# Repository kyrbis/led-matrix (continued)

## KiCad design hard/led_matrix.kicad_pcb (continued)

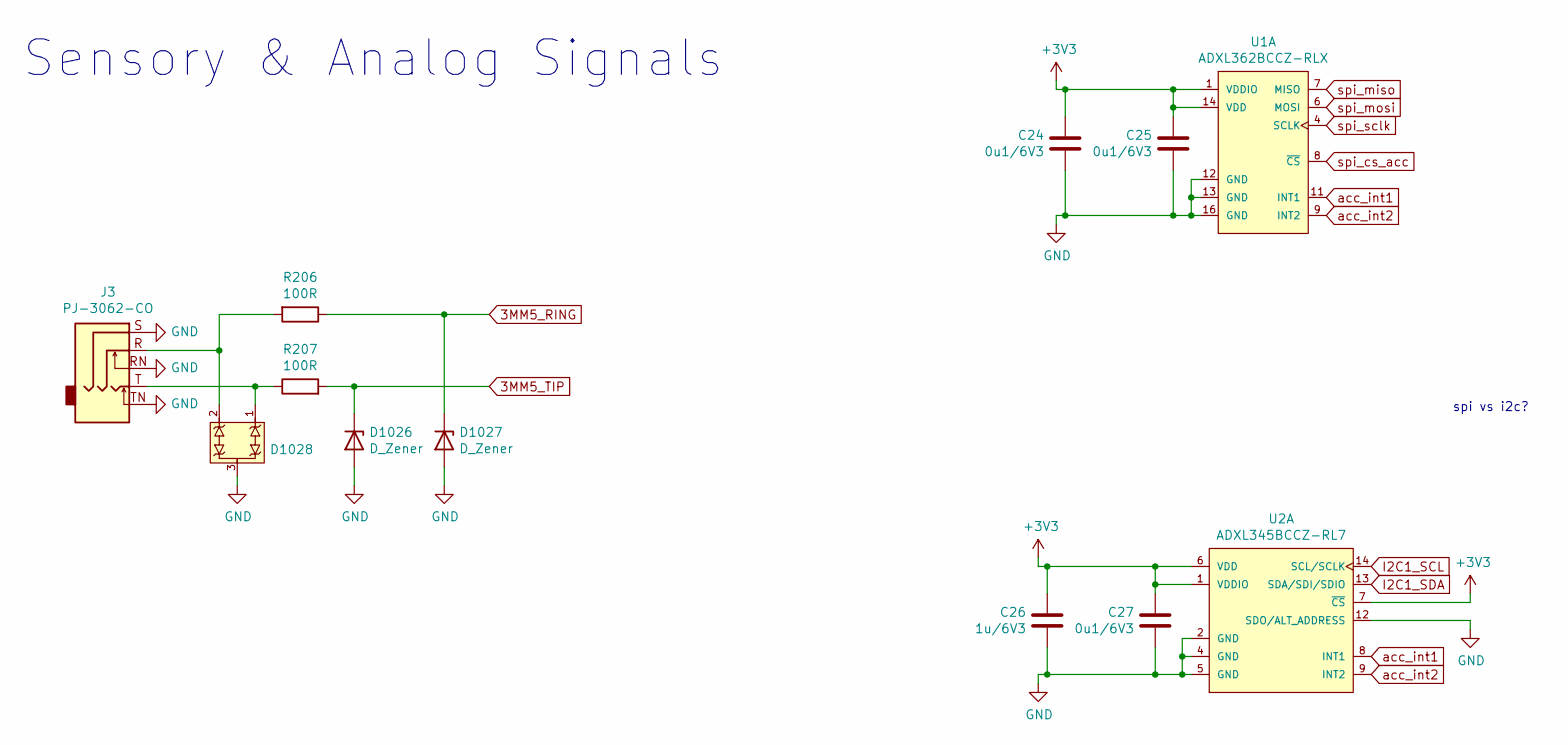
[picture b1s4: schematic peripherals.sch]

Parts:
C24, C25, C27: 0u1/6V3; C_0402_1005Metric
C26: 1u/6V3; C_0603_1608Metric
D1026, D1027: D_Zener; D_MiniMELF; MPN Semtech; JLCPCB_Part_Number C8056
D1028: PSM712-LF-T7; SOT-23; MPN PSM712-LF-T7; JLCPCB_Part_Number C32677
J3: PJ-3062-CO; Connectors_XKB Connectivity_PJ-3062-CO; MPN PJ-3062-CO; JLCPCB_Part_Number C319113
R206, R207: 100R; R_0603_1608Metric
U1: ADXL362BCCZ-RLX; Sensors_AnalogDevices_ADXL362BCCZ-RX; MPN ADXL362BCCZ-RL; DigiKey_Part_Number ADXL362BCCZ-RL7CT-ND
U2: ADXL345BCCZ-RL7; Sensors_AnalogDevices_ADXL345BCCZ-RL; MPN ADXL345BCCZ-RL7; DigiKey_Part_Number ADXL345BCCZ-RLCT-ND

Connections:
+3V3: C24.2, C25.2, C26.2, C27.2, U1.1 (VDDIO), U1.14 (VDD), U2.1 (VDDIO), U2.6 (VDD), U2.7 (~CS~); also elsewhere on the board
GND: C24.1, C25.1, C26.1, C27.1, D1026.2 (A), D1027.2 (A), D1028.3, J3.RN, J3.S, J3.TN, U1.12 (GND), U1.13 (GND), U1.16 (GND), U2.2 (GND), U2.4 (GND), U2.5 (GND), U2.12 (SDO/ALT_ADDRESS); also elsewhere on the board
I2C1_SCL: U2.14 (SCL/SCLK); also elsewhere on the board
I2C1_SDA: U2.13 (SDA/SDI/SDIO); also elsewhere on the board
unnamed: D1028.1, J3.T, R207.1
unnamed: D1028.2, J3.R, R206.2
acc_int1: U1.11 (INT1), U2.8 (INT1)
acc_int2: U1.9 (INT2), U2.9 (INT2)
analog_ring: D1027.1 (K), R206.1
analog_tip: D1026.1 (K), R207.2

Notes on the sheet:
spi vs i2c?
Sensory & Analog Signals

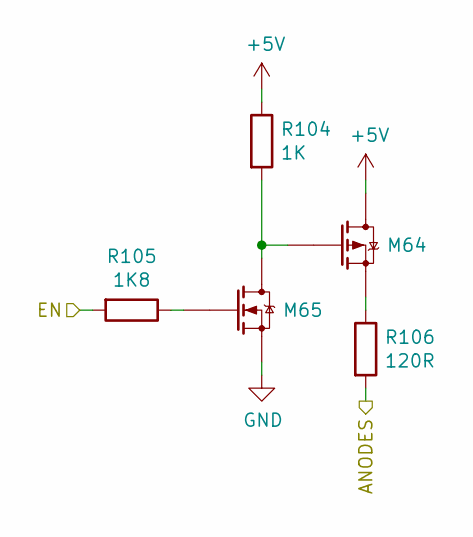
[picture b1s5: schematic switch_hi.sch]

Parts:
M2: IRLML6402TRPBF; SOT-23; Mouser_Part_Number 942-IRLML6402TRPBF; DigiKey_Part_Number IRLML6402PBFTR-ND
M3: 2N7002,215; SOT-23; MPN 2N7002,215; JLCPCB_Part_Number C65189
R11: 1K; R_0402_1005Metric
R12: 1K8; R_0402_1005Metric
R13: 120R; R_1210_3225Metric

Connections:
+5V: M2.3 (D), R11.1; also elsewhere on the board
/led matrix/common anode/ANODES: R13.2; also elsewhere on the board
GND: M3.2 (S); also elsewhere on the board
unnamed: M2.1 (G), M3.3 (D), R11.2
unnamed: M2.2 (S), R13.1
unnamed: M3.1 (G), R12.1
x0: R12.2; also elsewhere on the board

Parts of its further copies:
M4, M6, M8, M10, M12, M14, M16, M18, M20, M22, M24, M26, M28, M30, M32, M34, M36, M38, M40, M42, M44, M46, M48, M50, M52, M54, M56, M58, M60, M62, M64: IRLML6402TRPBF; SOT-23; Mouser_Part_Number 942-IRLML6402TRPBF; DigiKey_Part_Number IRLML6402PBFTR-ND
M5, M7, M9, M11, M13, M15, M17, M19, M21, M23, M25, M27, M29, M31, M33, M35, M37, M39, M41, M43, M45, M47, M49, M51, M53, M55, M57, M59, M61, M63, M65: 2N7002,215; SOT-23; MPN 2N7002,215; JLCPCB_Part_Number C65189
R14, R17, R20, R23, R26, R29, R32, R35, R38, R41, R44, R47, R50, R53, R56, R59, R62, R65, R68, R71, R74, R77, R80, R83, R86, R89, R92, R95, R98, R101, R104: 1K; R_0402_1005Metric
R15, R18, R21, R24, R27, R30, R33, R36, R39, R42, R45, R48, R51, R54, R57, R60, R63, R66, R69, R72, R75, R78, R81, R84, R87, R90, R93, R96, R99, R102, R105: 1K8; R_0402_1005Metric
R16, R19, R22, R25, R28, R31, R34, R37, R40, R43, R46, R49, R52, R55, R58, R61, R64, R67, R70, R73, R76, R79, R82, R85, R88, R91, R94, R97, R100, R103, R106: 120R; R_1210_3225Metric

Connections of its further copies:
+5V: M4.3 (D), M6.3 (D), M8.3 (D), M10.3 (D), M12.3 (D), M14.3 (D), M16.3 (D), M18.3 (D), M20.3 (D), M22.3 (D), M24.3 (D), M26.3 (D), M28.3 (D), M30.3 (D), M32.3 (D), M34.3 (D), M36.3 (D), M38.3 (D), M40.3 (D), M42.3 (D), M44.3 (D), M46.3 (D), M48.3 (D), M50.3 (D), M52.3 (D), M54.3 (D), M56.3 (D), M58.3 (D), M60.3 (D), M62.3 (D), M64.3 (D), R14.1, R17.1, R20.1, R23.1, R26.1, R29.1, R32.1, R35.1, R38.1, R41.1, R44.1, R47.1, R50.1, R53.1, R56.1, R59.1, R62.1, R65.1, R68.1, R71.1, R74.1, R77.1, R80.1, R83.1, R86.1, R89.1, R92.1, R95.1, R98.1, R101.1, R104.1; also elsewhere on the board
/led matrix/sheet9E2197FD/ANODES: R16.2; also elsewhere on the board
/led matrix/sheetA3FD3BF7/ANODES: R31.2; also elsewhere on the board
/led matrix/sheetA3FD3BF8/ANODES: R34.2; also elsewhere on the board
/led matrix/sheetA4B98B8A/ANODES: R49.2; also elsewhere on the board
/led matrix/sheetA4B98B8B/ANODES: R52.2; also elsewhere on the board
/led matrix/sheetA4B98B8C/ANODES: R55.2; also elsewhere on the board
/led matrix/sheetA4B98B8D/ANODES: R58.2; also elsewhere on the board
/led matrix/sheetA4B98B86/ANODES: R37.2; also elsewhere on the board
/led matrix/sheetA4B98B87/ANODES: R40.2; also elsewhere on the board
/led matrix/sheetA4B98B88/ANODES: R43.2; also elsewhere on the board
/led matrix/sheetA4B98B89/ANODES: R46.2; also elsewhere on the board
/led matrix/sheetA10E8493/ANODES: R19.2; also elsewhere on the board
/led matrix/sheetA10E8494/ANODES: R22.2; also elsewhere on the board
/led matrix/sheetA341C37F/ANODES: R25.2; also elsewhere on the board
/led matrix/sheetA341C380/ANODES: R28.2; also elsewhere on the board
/led matrix/sheetA575BE8D/ANODES: R61.2; also elsewhere on the board
/led matrix/sheetA575BE8E/ANODES: R64.2; also elsewhere on the board
/led matrix/sheetA575BE8F/ANODES: R67.2; also elsewhere on the board
/led matrix/sheetA575BE9A/ANODES: R100.2; also elsewhere on the board
/led matrix/sheetA575BE9B/ANODES: R103.2; also elsewhere on the board
/led matrix/sheetA575BE9C/ANODES: R106.2; also elsewhere on the board
/led matrix/sheetA575BE90/ANODES: R70.2; also elsewhere on the board
/led matrix/sheetA575BE91/ANODES: R73.2; also elsewhere on the board
/led matrix/sheetA575BE92/ANODES: R76.2; also elsewhere on the board
/led matrix/sheetA575BE93/ANODES: R79.2; also elsewhere on the board
/led matrix/sheetA575BE94/ANODES: R82.2; also elsewhere on the board
/led matrix/sheetA575BE95/ANODES: R85.2; also elsewhere on the board
/led matrix/sheetA575BE96/ANODES: R88.2; also elsewhere on the board
/led matrix/sheetA575BE97/ANODES: R91.2; also elsewhere on the board
/led matrix/sheetA575BE98/ANODES: R94.2; also elsewhere on the board
/led matrix/sheetA575BE99/ANODES: R97.2; also elsewhere on the board
GND: M5.2 (S), M7.2 (S), M9.2 (S), M11.2 (S), M13.2 (S), M15.2 (S), M17.2 (S), M19.2 (S), M21.2 (S), M23.2 (S), M25.2 (S), M27.2 (S), M29.2 (S), M31.2 (S), M33.2 (S), M35.2 (S), M37.2 (S), M39.2 (S), M41.2 (S), M43.2 (S), M45.2 (S), M47.2 (S), M49.2 (S), M51.2 (S), M53.2 (S), M55.2 (S), M57.2 (S), M59.2 (S), M61.2 (S), M63.2 (S), M65.2 (S); also elsewhere on the board
unnamed: M4.1 (G), M5.3 (D), R14.2
unnamed: M4.2 (S), R16.1
unnamed: M5.1 (G), R15.1
unnamed: M6.1 (G), M7.3 (D), R17.2
unnamed: M6.2 (S), R19.1
unnamed: M7.1 (G), R18.1
unnamed: M8.1 (G), M9.3 (D), R20.2
unnamed: M8.2 (S), R22.1
unnamed: M9.1 (G), R21.1
unnamed: M10.1 (G), M11.3 (D), R23.2
unnamed: M10.2 (S), R25.1
unnamed: M11.1 (G), R24.1
unnamed: M12.1 (G), M13.3 (D), R26.2
unnamed: M12.2 (S), R28.1
unnamed: M13.1 (G), R27.1
unnamed: M14.1 (G), M15.3 (D), R29.2
unnamed: M14.2 (S), R31.1
unnamed: M15.1 (G), R30.1
unnamed: M16.1 (G), M17.3 (D), R32.2
unnamed: M16.2 (S), R34.1
unnamed: M17.1 (G), R33.1
unnamed: M18.1 (G), M19.3 (D), R35.2
unnamed: M18.2 (S), R37.1
unnamed: M19.1 (G), R36.1
unnamed: M20.1 (G), M21.3 (D), R38.2
unnamed: M20.2 (S), R40.1
unnamed: M21.1 (G), R39.1
unnamed: M22.1 (G), M23.3 (D), R41.2
unnamed: M22.2 (S), R43.1
unnamed: M23.1 (G), R42.1
unnamed: M24.1 (G), M25.3 (D), R44.2
unnamed: M24.2 (S), R46.1
unnamed: M25.1 (G), R45.1
unnamed: M26.1 (G), M27.3 (D), R47.2
unnamed: M26.2 (S), R49.1
unnamed: M27.1 (G), R48.1
unnamed: M28.1 (G), M29.3 (D), R50.2
unnamed: M28.2 (S), R52.1
unnamed: M29.1 (G), R51.1
unnamed: M30.1 (G), M31.3 (D), R53.2
unnamed: M30.2 (S), R55.1
unnamed: M31.1 (G), R54.1
unnamed: M32.1 (G), M33.3 (D), R56.2
unnamed: M32.2 (S), R58.1
unnamed: M33.1 (G), R57.1
unnamed: M34.1 (G), M35.3 (D), R59.2
unnamed: M34.2 (S), R61.1
unnamed: M35.1 (G), R60.1
unnamed: M36.1 (G), M37.3 (D), R62.2
unnamed: M36.2 (S), R64.1
unnamed: M37.1 (G), R63.1
unnamed: M38.1 (G), M39.3 (D), R65.2
unnamed: M38.2 (S), R67.1
unnamed: M39.1 (G), R66.1
unnamed: M40.1 (G), M41.3 (D), R68.2
unnamed: M40.2 (S), R70.1
unnamed: M41.1 (G), R69.1
unnamed: M42.1 (G), M43.3 (D), R71.2
unnamed: M42.2 (S), R73.1
unnamed: M43.1 (G), R72.1
unnamed: M44.1 (G), M45.3 (D), R74.2
unnamed: M44.2 (S), R76.1
unnamed: M45.1 (G), R75.1
unnamed: M46.1 (G), M47.3 (D), R77.2
unnamed: M46.2 (S), R79.1
unnamed: M47.1 (G), R78.1
unnamed: M48.1 (G), M49.3 (D), R80.2
unnamed: M48.2 (S), R82.1
unnamed: M49.1 (G), R81.1
unnamed: M50.1 (G), M51.3 (D), R83.2
unnamed: M50.2 (S), R85.1
unnamed: M51.1 (G), R84.1
unnamed: M52.1 (G), M53.3 (D), R86.2
unnamed: M52.2 (S), R88.1
unnamed: M53.1 (G), R87.1
unnamed: M54.1 (G), M55.3 (D), R89.2
unnamed: M54.2 (S), R91.1
unnamed: M55.1 (G), R90.1
unnamed: M56.1 (G), M57.3 (D), R92.2
unnamed: M56.2 (S), R94.1
unnamed: M57.1 (G), R93.1
unnamed: M58.1 (G), M59.3 (D), R95.2
unnamed: M58.2 (S), R97.1
unnamed: M59.1 (G), R96.1
unnamed: M60.1 (G), M61.3 (D), R98.2
unnamed: M60.2 (S), R100.1
unnamed: M61.1 (G), R99.1
unnamed: M62.1 (G), M63.3 (D), R101.2
unnamed: M62.2 (S), R103.1
unnamed: M63.1 (G), R102.1
unnamed: M64.1 (G), M65.3 (D), R104.2
unnamed: M64.2 (S), R106.1
unnamed: M65.1 (G), R105.1
SWCLK: R54.2; also elsewhere on the board
SWDIO: R51.2; also elsewhere on the board
x1: R15.2; also elsewhere on the board
x2: R18.2; also elsewhere on the board
x3: R21.2; also elsewhere on the board
x4: R24.2; also elsewhere on the board
x5: R27.2; also elsewhere on the board
x6: R30.2; also elsewhere on the board
x7: R33.2; also elsewhere on the board
x8: R36.2; also elsewhere on the board
x9: R39.2; also elsewhere on the board
x10: R42.2; also elsewhere on the board
x11: R45.2; also elsewhere on the board
x12: R48.2; also elsewhere on the board
x15: R57.2; also elsewhere on the board
x16: R60.2; also elsewhere on the board
x17: R63.2; also elsewhere on the board
x18: R66.2; also elsewhere on the board
x19: R69.2; also elsewhere on the board
x20: R72.2; also elsewhere on the board
x21: R75.2; also elsewhere on the board
x22: R78.2; also elsewhere on the board
x23: R81.2; also elsewhere on the board
x24: R84.2; also elsewhere on the board
x25: R87.2; also elsewhere on the board
x26: R90.2; also elsewhere on the board
x27: R93.2; also elsewhere on the board
x28: R96.2; also elsewhere on the board
x29: R99.2; also elsewhere on the board
x30: R102.2; also elsewhere on the board
x31: R105.2; also elsewhere on the board

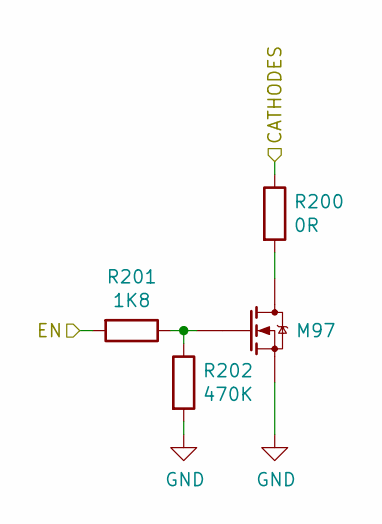
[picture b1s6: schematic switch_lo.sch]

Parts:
M66: IRLML0030TRPBF; SOT-23; Mouser_Part_Number 942-IRLML0030TRPBF; DigiKey_Part_Number IRLML0030TRPBFCT-ND
R107: 0R; R_1210_3225Metric
R108: 1K8; R_0402_1005Metric
R109: 470K; R_0402_1005Metric

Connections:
/led matrix/common cathode/CATHODES: R107.1; also elsewhere on the board
GND: M66.2 (S), R109.2; also elsewhere on the board
unnamed: M66.1 (G), R108.1, R109.1
unnamed: M66.3 (D), R107.2
y0: R108.2; also elsewhere on the board

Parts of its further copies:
M67, M68, M69, M70, M71, M72, M73, M74, M75, M76, M77, M78, M79, M80, M81, M82, M83, M84, M85, M86, M87, M88, M89, M90, M91, M92, M93, M94, M95, M96, M97: IRLML0030TRPBF; SOT-23; Mouser_Part_Number 942-IRLML0030TRPBF; DigiKey_Part_Number IRLML0030TRPBFCT-ND
R110, R113, R116, R119, R122, R125, R128, R131, R134, R137, R140, R143, R146, R149, R152, R155, R158, R161, R164, R167, R170, R173, R176, R179, R182, R185, R188, R191, R194, R197, R200: 0R; R_1210_3225Metric
R111, R114, R117, R120, R123, R126, R129, R132, R135, R138, R141, R144, R147, R150, R153, R156, R159, R162, R165, R168, R171, R174, R177, R180, R183, R186, R189, R192, R195, R198, R201: 1K8; R_0402_1005Metric
R112, R115, R118, R121, R124, R127, R130, R133, R136, R139, R142, R145, R148, R151, R154, R157, R160, R163, R166, R169, R172, R175, R178, R181, R184, R187, R190, R193, R196, R199, R202: 470K; R_0402_1005Metric

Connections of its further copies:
/led matrix/sheetD7D8B720/CATHODES: R110.1; also elsewhere on the board
/led matrix/sheetD89BE98B/CATHODES: R113.1; also elsewhere on the board
/led matrix/sheetD89BE98C/CATHODES: R116.1; also elsewhere on the board
/led matrix/sheetD95F2321/CATHODES: R119.1; also elsewhere on the board
/led matrix/sheetD95F2322/CATHODES: R122.1; also elsewhere on the board
/led matrix/sheetD95F2323/CATHODES: R125.1; also elsewhere on the board
/led matrix/sheetD95F2324/CATHODES: R128.1; also elsewhere on the board
/led matrix/sheetDA22614D/CATHODES: R131.1; also elsewhere on the board
/led matrix/sheetDA22614E/CATHODES: R134.1; also elsewhere on the board
/led matrix/sheetDA22614F/CATHODES: R137.1; also elsewhere on the board
/led matrix/sheetDA226150/CATHODES: R140.1; also elsewhere on the board
/led matrix/sheetDA226151/CATHODES: R143.1; also elsewhere on the board
/led matrix/sheetDA226152/CATHODES: R146.1; also elsewhere on the board
/led matrix/sheetDA226153/CATHODES: R149.1; also elsewhere on the board
/led matrix/sheetDA226154/CATHODES: R152.1; also elsewhere on the board
/led matrix/sheetDAE5EEF6/CATHODES: R155.1; also elsewhere on the board
/led matrix/sheetDAE5EEF7/CATHODES: R158.1; also elsewhere on the board
/led matrix/sheetDAE5EEF8/CATHODES: R161.1; also elsewhere on the board
/led matrix/sheetDAE5EEF9/CATHODES: R164.1; also elsewhere on the board
/led matrix/sheetDAE5EEFA/CATHODES: R167.1; also elsewhere on the board
/led matrix/sheetDAE5EEFB/CATHODES: R170.1; also elsewhere on the board
/led matrix/sheetDAE5EEFC/CATHODES: R173.1; also elsewhere on the board
/led matrix/sheetDAE5EEFD/CATHODES: R176.1; also elsewhere on the board
/led matrix/sheetDAE5EEFE/CATHODES: R179.1; also elsewhere on the board
/led matrix/sheetDAE5EEFF/CATHODES: R182.1; also elsewhere on the board
/led matrix/sheetDAE5EF00/CATHODES: R185.1; also elsewhere on the board
/led matrix/sheetDAE5EF01/CATHODES: R188.1; also elsewhere on the board
/led matrix/sheetDAE5EF02/CATHODES: R191.1; also elsewhere on the board
/led matrix/sheetDAE5EF03/CATHODES: R194.1; also elsewhere on the board
/led matrix/sheetDAE5EF04/CATHODES: R197.1; also elsewhere on the board
/led matrix/sheetDAE5EF05/CATHODES: R200.1; also elsewhere on the board
GND: M67.2 (S), M68.2 (S), M69.2 (S), M70.2 (S), M71.2 (S), M72.2 (S), M73.2 (S), M74.2 (S), M75.2 (S), M76.2 (S), M77.2 (S), M78.2 (S), M79.2 (S), M80.2 (S), M81.2 (S), M82.2 (S), M83.2 (S), M84.2 (S), M85.2 (S), M86.2 (S), M87.2 (S), M88.2 (S), M89.2 (S), M90.2 (S), M91.2 (S), M92.2 (S), M93.2 (S), M94.2 (S), M95.2 (S), M96.2 (S), M97.2 (S), R112.2, R115.2, R118.2, R121.2, R124.2, R127.2, R130.2, R133.2, R136.2, R139.2, R142.2, R145.2, R148.2, R151.2, R154.2, R157.2, R160.2, R163.2, R166.2, R169.2, R172.2, R175.2, R178.2, R181.2, R184.2, R187.2, R190.2, R193.2, R196.2, R199.2, R202.2; also elsewhere on the board
unnamed: M67.1 (G), R111.1, R112.1
unnamed: M67.3 (D), R110.2
unnamed: M68.1 (G), R114.1, R115.1
unnamed: M68.3 (D), R113.2
unnamed: M69.1 (G), R117.1, R118.1
unnamed: M69.3 (D), R116.2
unnamed: M70.1 (G), R120.1, R121.1
unnamed: M70.3 (D), R119.2
unnamed: M71.1 (G), R123.1, R124.1
unnamed: M71.3 (D), R122.2
unnamed: M72.1 (G), R126.1, R127.1
unnamed: M72.3 (D), R125.2
unnamed: M73.1 (G), R129.1, R130.1
unnamed: M73.3 (D), R128.2
unnamed: M74.1 (G), R132.1, R133.1
unnamed: M74.3 (D), R131.2
unnamed: M75.1 (G), R135.1, R136.1
unnamed: M75.3 (D), R134.2
unnamed: M76.1 (G), R138.1, R139.1
unnamed: M76.3 (D), R137.2
unnamed: M77.1 (G), R141.1, R142.1
unnamed: M77.3 (D), R140.2
unnamed: M78.1 (G), R144.1, R145.1
unnamed: M78.3 (D), R143.2
unnamed: M79.1 (G), R147.1, R148.1
unnamed: M79.3 (D), R146.2
unnamed: M80.1 (G), R150.1, R151.1
unnamed: M80.3 (D), R149.2
unnamed: M81.1 (G), R153.1, R154.1
unnamed: M81.3 (D), R152.2
unnamed: M82.1 (G), R156.1, R157.1
unnamed: M82.3 (D), R155.2
unnamed: M83.1 (G), R159.1, R160.1
unnamed: M83.3 (D), R158.2
unnamed: M84.1 (G), R162.1, R163.1
unnamed: M84.3 (D), R161.2
unnamed: M85.1 (G), R165.1, R166.1
unnamed: M85.3 (D), R164.2
unnamed: M86.1 (G), R168.1, R169.1
unnamed: M86.3 (D), R167.2
unnamed: M87.1 (G), R171.1, R172.1
unnamed: M87.3 (D), R170.2
unnamed: M88.1 (G), R174.1, R175.1
unnamed: M88.3 (D), R173.2
unnamed: M89.1 (G), R177.1, R178.1
unnamed: M89.3 (D), R176.2
unnamed: M90.1 (G), R180.1, R181.1
unnamed: M90.3 (D), R179.2
unnamed: M91.1 (G), R183.1, R184.1
unnamed: M91.3 (D), R182.2
unnamed: M92.1 (G), R186.1, R187.1
unnamed: M92.3 (D), R185.2
unnamed: M93.1 (G), R189.1, R190.1
unnamed: M93.3 (D), R188.2
unnamed: M94.1 (G), R192.1, R193.1
unnamed: M94.3 (D), R191.2
unnamed: M95.1 (G), R195.1, R196.1
unnamed: M95.3 (D), R194.2
unnamed: M96.1 (G), R198.1, R199.1
unnamed: M96.3 (D), R197.2
unnamed: M97.1 (G), R201.1, R202.1
unnamed: M97.3 (D), R200.2
y1: R111.2; also elsewhere on the board
y2: R114.2; also elsewhere on the board
y3: R117.2; also elsewhere on the board
y4: R120.2; also elsewhere on the board
y5: R123.2; also elsewhere on the board
y6: R126.2; also elsewhere on the board
y7: R129.2; also elsewhere on the board
y8: R132.2; also elsewhere on the board
y9: R135.2; also elsewhere on the board
y10: R138.2; also elsewhere on the board
y11: R141.2; also elsewhere on the board
y12: R144.2; also elsewhere on the board
y13: R147.2; also elsewhere on the board
y14: R150.2; also elsewhere on the board
y15: R153.2; also elsewhere on the board
y16: R156.2; also elsewhere on the board
y17: R159.2; also elsewhere on the board
y18: R162.2; also elsewhere on the board
y19: R165.2; also elsewhere on the board
y20: R168.2; also elsewhere on the board
y21: R171.2; also elsewhere on the board
y22: R174.2; also elsewhere on the board
y23: R177.2; also elsewhere on the board
y24: R180.2; also elsewhere on the board
y25: R183.2; also elsewhere on the board
y26: R186.2; also elsewhere on the board
y27: R189.2; also elsewhere on the board
y28: R192.2; also elsewhere on the board
y29: R195.2; also elsewhere on the board
y30: R198.2; also elsewhere on the board
y31: R201.2; also elsewhere on the board

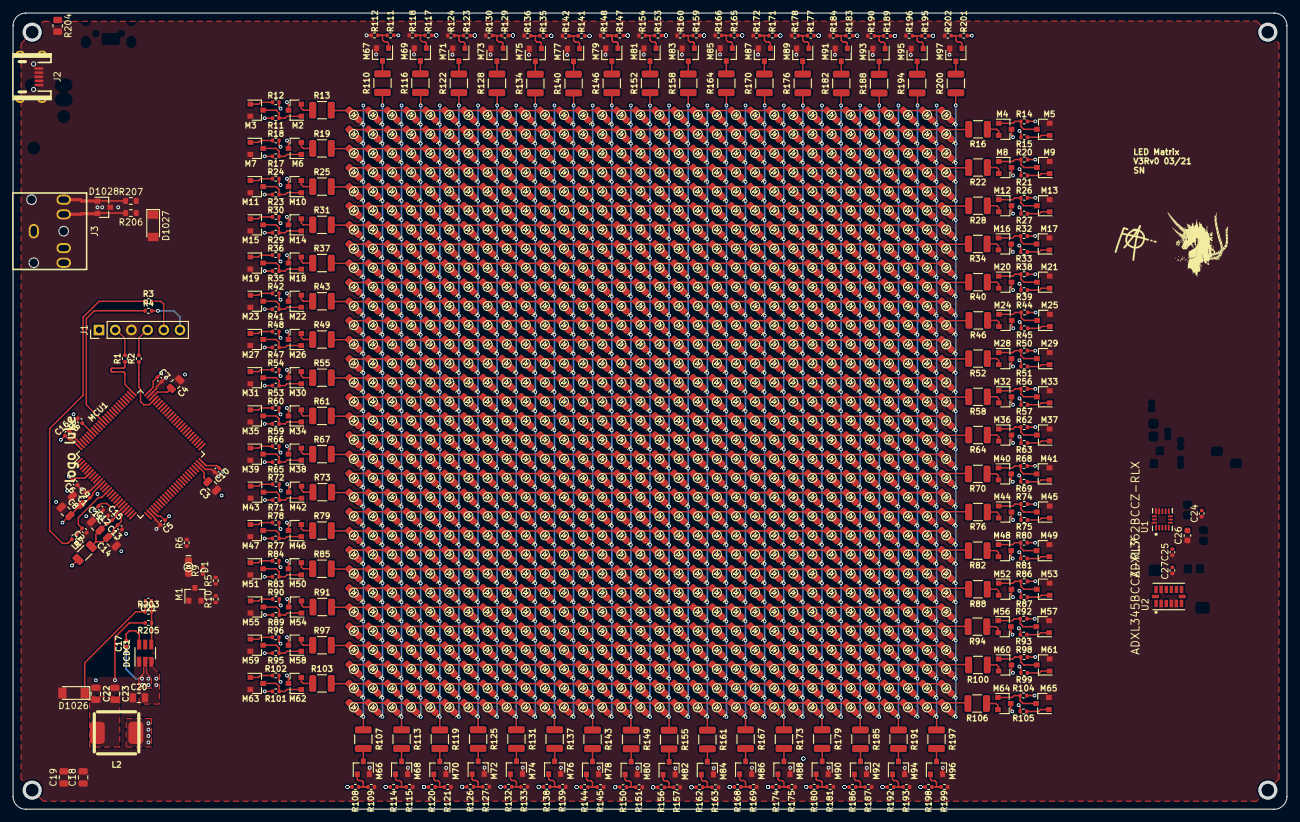
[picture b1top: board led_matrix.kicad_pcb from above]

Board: 4 copper layers, 200.0 x 125.0 mm, 1368 parts (0 on the bottom side), 318 nets.

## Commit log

2021-03-19 initial folder structure
2021-03-19 folder structure refactor
2021-03-19 Update README.md
    Added an exclamation points
2021-03-19 refactoringering
2021-03-19 Create LTST-S270TBKT.kicad_mod
    Added Footprint library
    -Footprint for LTST-S237BKT LED
2021-03-19 uc symbol creation
2021-03-19 mcu sym update
2021-03-19 pin swap + package select
2021-03-19 debug for kaese
2021-03-19 main led insert
2021-03-19 updated for new footprint lib
2021-03-19 Modified Footprint
    Modified Footprint:
    LED_LiteOn_LTST-S270TBKT
    -Changed Cathode Indicator on Footprint diode symbol
    -Added a 3D Model for the LED
2021-03-19 3d files naming consistency
2021-03-20 added various devices
2021-03-20 update for kaese
2021-03-20 refactor
2021-03-20 finished dc dc schematic
2021-03-20 added 3d model for dc dc inductor
2021-03-20 updated 3d model
2021-03-20 added usb connector
2021-03-20 3d model update
2021-03-20 signal nmos added
2021-03-20 Update led_matrix.lib
    Naming Bugfix
    -LED Symbol pins had the wrong name
2021-03-20 added adxl362
2021-03-20 RIIIIIIIIIIIIIBSSSSSS!!!!
    Rib break
2021-03-20 cleanup
2021-03-20 added sensors
2021-03-20 32x32 leds on board
2021-03-20 added vias
2021-03-21 led matrix schematic page completed
2021-03-21 pc format refactor wip
    @lukekaese leds still need to be attenuated
2021-03-21 format/outline update
2021-03-21 led numbering by @lukekaese
2021-03-21 mcu progress sync to pcb
2021-03-21 added matrix cross connections (ampacity per line @0.7A)
2021-03-21 layouting update
2021-03-21 driver nmos update
2021-03-21 uc minimum application
2021-03-21 connected uc to matrix line driver signals
2021-03-21 Backup LEDdriver progress
2021-03-21 Added All the FETs
    All the FETs were Added
    And it looks awsome
2021-03-21 added led driver layout by @lukekaese
2021-03-21 pcb format refactor
2021-03-22 general layout update
2021-03-22 courtyard update
2021-03-22 removed value visibility
2021-03-22 footprint adjustment to fit drc
2021-03-22 layout process
2021-03-22 drc fix
2021-03-22 layout progress. todo: led drivers
2021-03-22 Ground Vias + Logo Placeholder
    Added Ground Vias to the N-MOS controling the P-MOS led drive
    Added a placeholder for my logo
2021-03-22 layout progress
2021-03-23 qr code to https://github.com/kyrbis/led-matrix
2021-03-23 release candidate. ready for review by @lukekaese
2021-03-23 attribute naming update
    JLCPCB_Part_Number -> LCSC
    DigiKey_Part_Number -> DigiKey
    Mouser_Part_Number -> Mouser
2021-03-23 re-connect footprints
2021-03-23 release candidate
    fixed sync issues
2021-03-23 adjusted some naming placement
2021-03-23 added description + 3d preview
2021-03-23 updated description
2021-03-23 adjusted vin track
2021-03-23 added logo + review
    added logo
    reviewed scematic
2021-03-23 v3rv0 release candidate
2021-03-23 added some GND vias
2021-03-23 made release
2021-03-23 edge fixes
2021-03-23 gerber process update
2021-03-23 removed stub
2021-03-23 updated footprints in preparation for connector 3d files
2021-03-23 3d update
2021-03-23 Added 3d-Model for Audioconnector ERROR WAS FOUND in Connenctor Footprint
2021-03-23 Revert "Added 3d-Model for Audioconnector ERROR WAS FOUND in Connenctor Footprint"
    This reverts commit f34c1a0b599020c2f06374e546637b903deb29e8.
2021-03-23 3d update for audio jack
2021-03-23 3D Connector
    Changed Color of step file for connector
    fixed femptos error in changing the z scale
    updated the pcb
2021-03-24 Added 3D Moddel for USB Connector Work In Progress
2021-03-24 Updated/Fixed 3D-Model
    I rushed a bit drawing the usb connektor yesterday so I fixed all the Errors i had in my
    Design. I think it is correct now.
    The Holes for the connector still need to be bigger
2021-03-24 usb connector package update + drc
2021-03-24 hole length update
2021-03-24 updated readme image
2021-03-24 release preparations
2021-03-24 release candidate
2021-03-24 added descriptions how to make new parts
2021-03-24 docu update
2021-03-26 updated dcdc + usb jack.
    release candidate, ready for review by @lukekaese
2021-03-26 added lcsc number for debug header
2021-03-26 bad step file
2021-03-27 updated all Earth vias size
2021-03-28 Added 3D-Model of the USB-Connector
2021-03-29 updated preview
